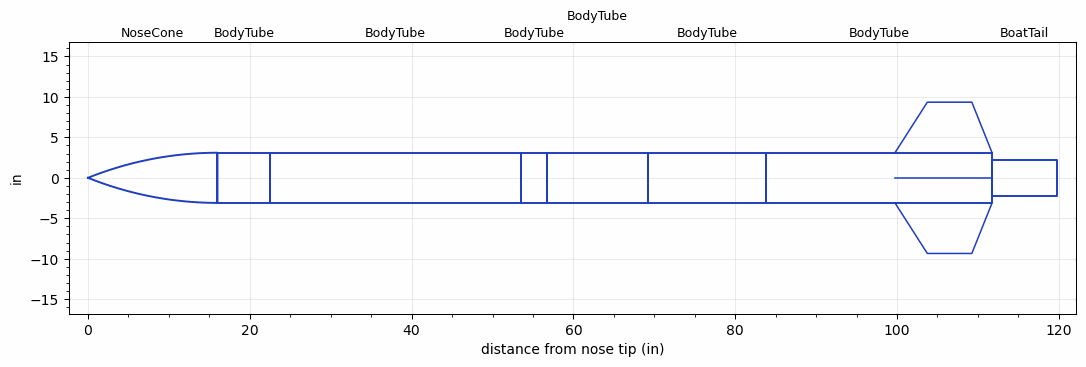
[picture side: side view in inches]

<RASAeroDocument>
 <FileVersion>2</FileVersion>
 <RocketDesign>
  <NoseCone>
   <Length>16</Length>
   <Diameter>6.2</Diameter>
   <Shape>Tangent Ogive</Shape>
   <Location>0</Location>
  </NoseCone>
  <BodyTube>
   <Length>6.5</Length>
   <Diameter>6.2</Diameter>
   <Location>16</Location>
  </BodyTube>
  <BodyTube>
   <Length>30.9999</Length>
   <Diameter>6.2</Diameter>
   <Location>22.5</Location>
  </BodyTube>
  <BodyTube>
   <Length>3.25</Length>
   <Diameter>6.2</Diameter>
   <Location>53.4999</Location>
  </BodyTube>
  <BodyTube>
   <Length>12.5</Length>
   <Diameter>6.2</Diameter>
   <Location>56.7499</Location>
  </BodyTube>
  <BodyTube>
   <Length>14.5</Length>
   <Diameter>6.2</Diameter>
   <Location>69.2499</Location>
  </BodyTube>
  <BodyTube>
   <Length>27.9999</Length>
   <Diameter>6.2</Diameter>
   <RailGuideDiameter>0.621</RailGuideDiameter>
   <RailGuideHeight>0.6845</RailGuideHeight>
   <Location>83.7498</Location>
   <Fin>
    <Count>4</Count>
    <Chord>12</Chord>
    <Span>6.25</Span>
    <SweepDistance>4</SweepDistance>
    <TipChord>5.5</TipChord>
    <Thickness>0.2</Thickness>
    <Location>12</Location>
    <AirfoilSection>Rounded</AirfoilSection>
   </Fin>
  </BodyTube>
  <BoatTail>
   <Length>8</Length>
   <Diameter>4.5</Diameter>
   <RearDiameter>4.5</RearDiameter>
   <Location>111.7498</Location>
  </BoatTail>
  <Surface>Sheet Metal</Surface>
  <CD>0</CD>
  <ModifiedBarrowman>False</ModifiedBarrowman>
  <Turbulence>False</Turbulence>
  <UseBooster1>False</UseBooster1>
  <UseBooster2>False</UseBooster2>
 </RocketDesign>
 <LaunchSite>
  <Altitude>2870.735</Altitude>
  <Pressure>28.9828</Pressure>
  <RodAngle>5</RodAngle>
  <RodLength>163.9997</RodLength>
  <Temperature>86</Temperature>
  <WindSpeed>0</WindSpeed>
 </LaunchSite>
 <Recovery>
  <Altitude1>1476.378</Altitude1>
  <Altitude2>656.168</Altitude2>
  <DeviceType1>Parachute</DeviceType1>
  <DeviceType2>Parachute</DeviceType2>
  <Event1>True</Event1>
  <Event2>True</Event2>
  <Size1>119.9998</Size1>
  <Size2>35.9999</Size2>
  <EventType1>Altitude</EventType1>
  <EventType2>Apogee</EventType2>
  <CD1>0.97</CD1>
  <CD2>0</CD2>
 </Recovery>
 <SimulationList>
  <Simulation>
   <SustainerLaunchWt>67.1418</SustainerLaunchWt>
   <SustainerCG>72.9033</SustainerCG>
   <SustainerIgnitionDelay>0</SustainerIgnitionDelay>
   <Booster1SeparationDelay>0</Booster1SeparationDelay>
   <Booster1IgnitionDelay>0</Booster1IgnitionDelay>
   <IncludeBooster1>False</IncludeBooster1>
   <Booster2Delay>0</Booster2Delay>
   <IncludeBooster2>False</IncludeBooster2>
  </Simulation>
 </SimulationList>
</RASAeroDocument>
